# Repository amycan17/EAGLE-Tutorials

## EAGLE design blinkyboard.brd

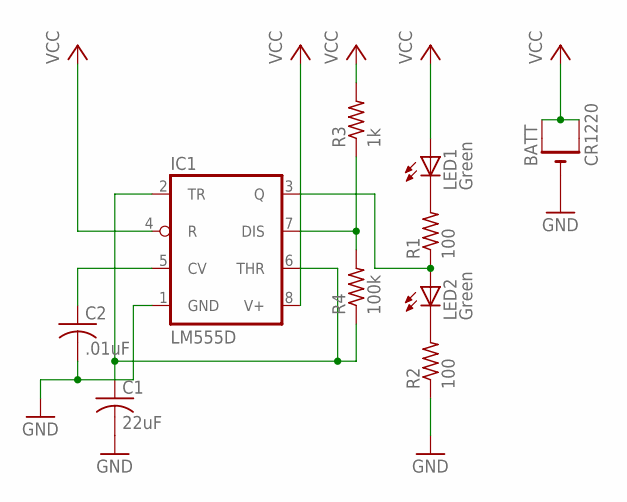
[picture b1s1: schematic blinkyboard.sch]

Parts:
BATT: CR1220; CR1220-SMD; MPN 3080
C1: 22uF; C0805; MPN 06035C224KAT2A
C2: .01uF; C0805; MPN CML103J100
IC1: LM555D; SO08; MPN TLC555CDR
LED1, LED2: Green; CHIPLED_0805; MPN SML-LX0805SUGC-TR
R1, R2: 100; R0805; MPN CRCW0805100RJNEA
R3: 1k; R0805; MPN CRCW08051K00FKEB
R4: 100k; R0805; MPN MCHP05W4F1003T5E

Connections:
GND: BATT.-, C1.2, C2.2, IC1.1 (GND), R2.1
unnamed: LED1.C, R1.2
unnamed: IC1.3 (Q), LED2.A, R1.1
unnamed: LED2.C, R2.2
unnamed: IC1.7 (DIS), R3.1, R4.2
unnamed: C2.1, IC1.5 (CV)
unnamed: C1.1, IC1.2 (TR), IC1.6 (THR), R4.1
VCC: BATT.+$1 (+), BATT.+$2 (+1), IC1.4 (R), IC1.8 (V+), LED1.A, R3.2

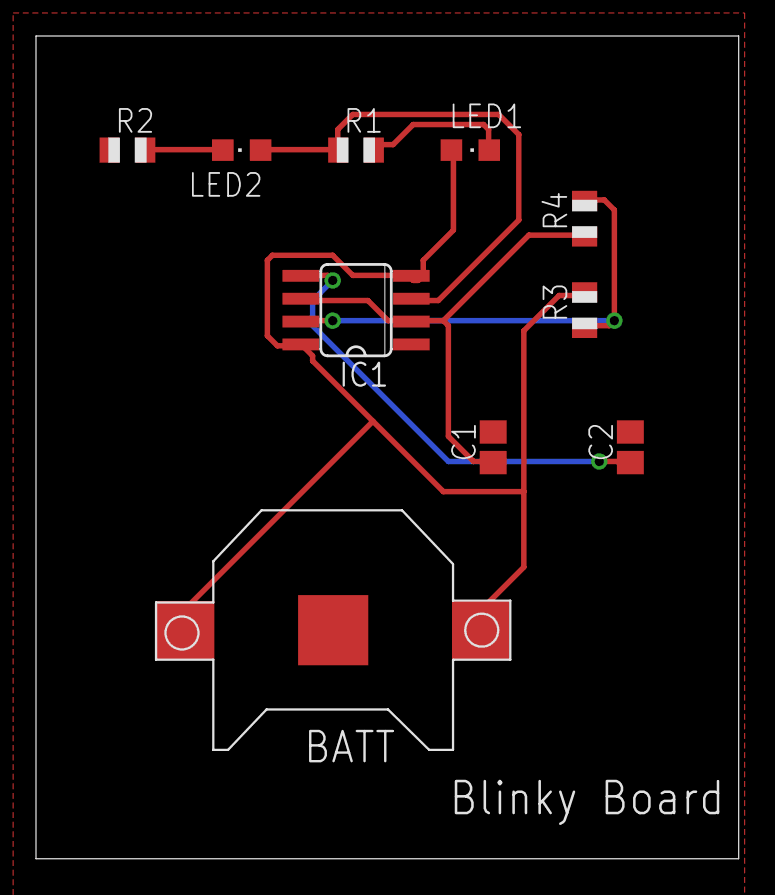
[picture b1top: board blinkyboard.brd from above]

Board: 2 copper layers, 39.0 x 45.7 mm, 10 parts (0 on the bottom side), 8 nets.

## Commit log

2020-04-12 Added .sch and .brd files
